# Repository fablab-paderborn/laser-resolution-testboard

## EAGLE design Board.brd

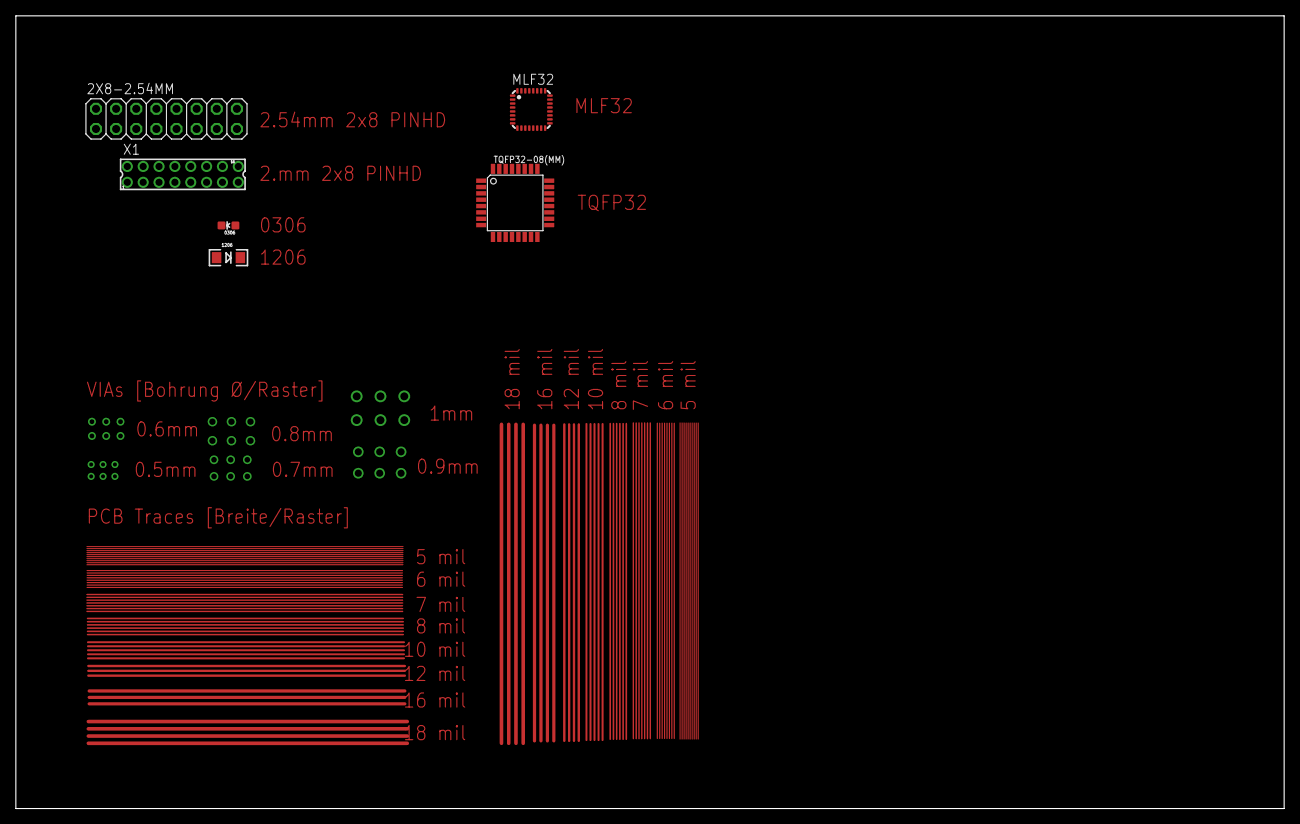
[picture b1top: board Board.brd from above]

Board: 2 copper layers, 160.0 x 100.0 mm, 6 parts (0 on the bottom side), 3 nets.

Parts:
2X8-2.54MM: 2X08
0306: LED-0603
1206: LED-1206
MLF32: MEGA8-MI; MLF32
TQFP32-08(MM): MEGA8-AI; TQFP32-08
X1: 332-16

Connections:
AVCC: MLF32.18, TQFP32-08(MM).18
GND: MLF32.3, MLF32.5, MLF32.21, TQFP32-08(MM).3, TQFP32-08(MM).5, TQFP32-08(MM).21
VCC: MLF32.4, MLF32.6, TQFP32-08(MM).4, TQFP32-08(MM).6

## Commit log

2015-06-04 Laser Resolution Test Board v.0.1
2015-06-05 More different formats

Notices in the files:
parts and their libraries:
SparkFun-LED: Licensing: Creative Commons ShareAlike 4.0 International - https://creativecommons.org/licenses/by-sa/4.0
